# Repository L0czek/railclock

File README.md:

# ESP32 Mainboard (Railclock-derived)

> A general-purpose ESP32-C6 module mainboard originally created for the Railclock project and redesigned as a generic controller and motor-power board.

This PCB exposes 11 GPIOs via JST connectors for sensors and actuators. It can run without an external 5V supply by using an on-board battery charger and a boost converter to create a 12V rail for motors and higher-power peripherals.

## Key Features

- 11 accessible GPIOs on JST connectors (5 ADC-capable ports on the left, 5 digital/drive outputs on the right).
- Left side ports: ADC-capable pins and a selectable 5V supply (powered by on-board 5V regulator/charger when available).
- Right side ports: digitally-driven output stage able to source up to 12V and ~800 mA (per port design limits depend on load and thermal conditions).
- On-board power management:
  - BQ24296M battery charger to accept battery power and produce the 5V line when no external USB is present.
  - PAM2421 boost converter to generate the 12V rail from the battery/5V bus.
- Motor driver: DRV8870 used to drive DC motors from the 12V rail.
- RTC clock MCP7940n with separate battery.

## Hardware Overview

- Connectors:
  - Left JST ports: ADC-capable pins. Expect up to 5V on these when the 5V supply is enabled — do not exceed 5V on ADC inputs.
  - Right JST ports: digital outputs with high-side/outstage to provide up to 12V for actuators.
- Power flow:
  - Primary charge/power management by the BQ24296M allows operation from a Li-ion battery without external 5V.
  - The PAM2421 boost converter takes the available rail and creates the 12V bus used by the outputs and motor driver.
- Motor driver:
  - DRV8870 drives DC motors using the 12V rail; follow the datasheet for current-limiting and heat-sinking requirements.

## Firmware

Firmware for this board is written in Rust and maintained in a separate repository: https://github.com/L0czek/esp32-mainboard

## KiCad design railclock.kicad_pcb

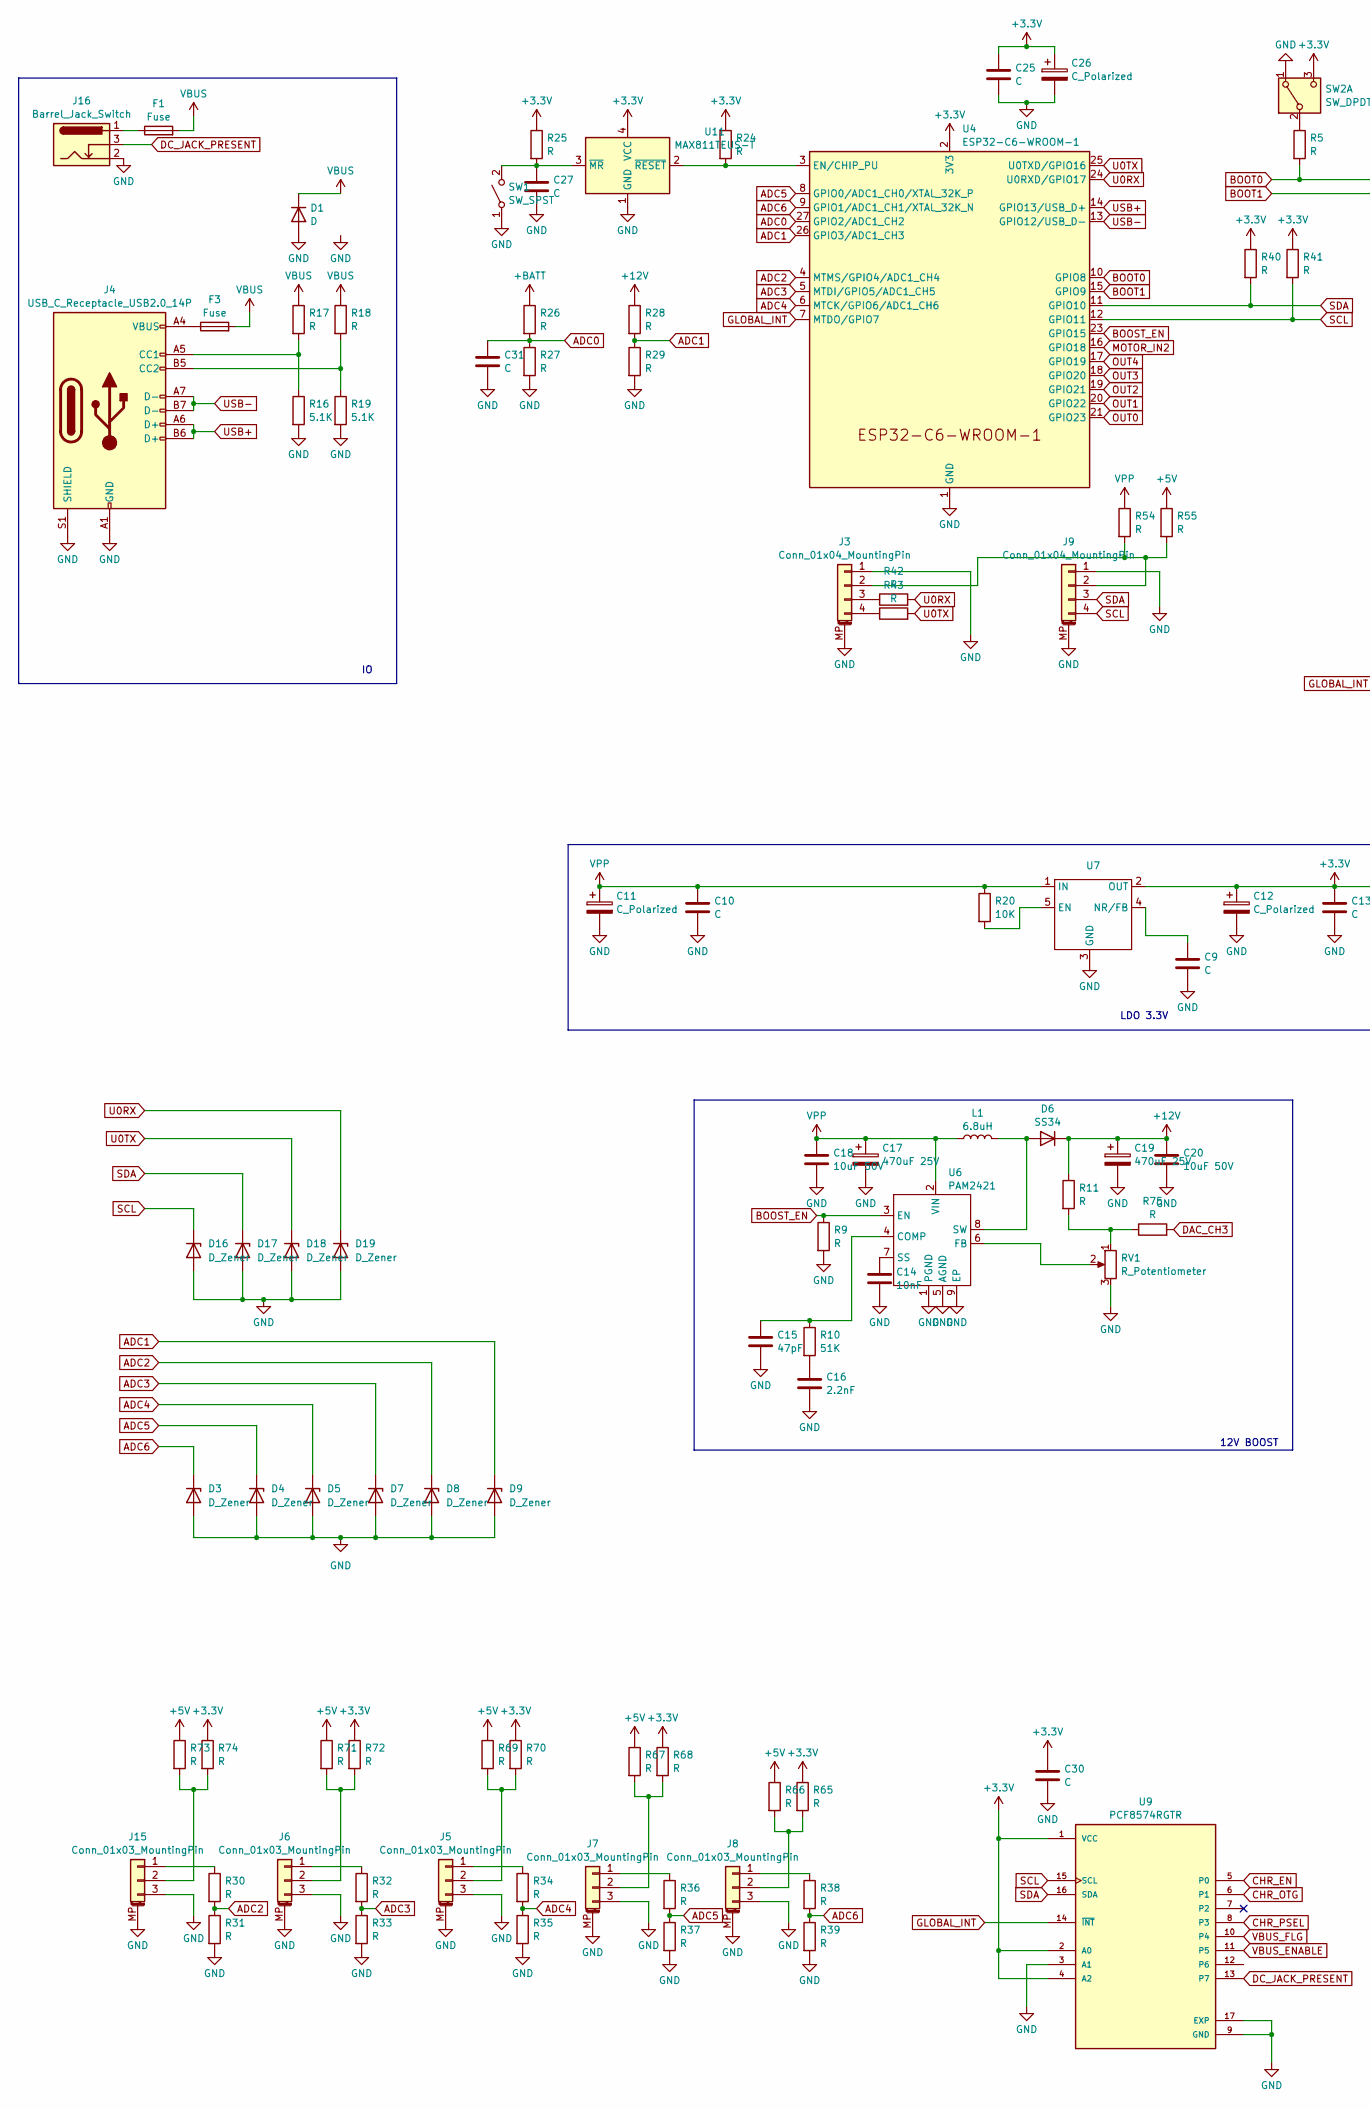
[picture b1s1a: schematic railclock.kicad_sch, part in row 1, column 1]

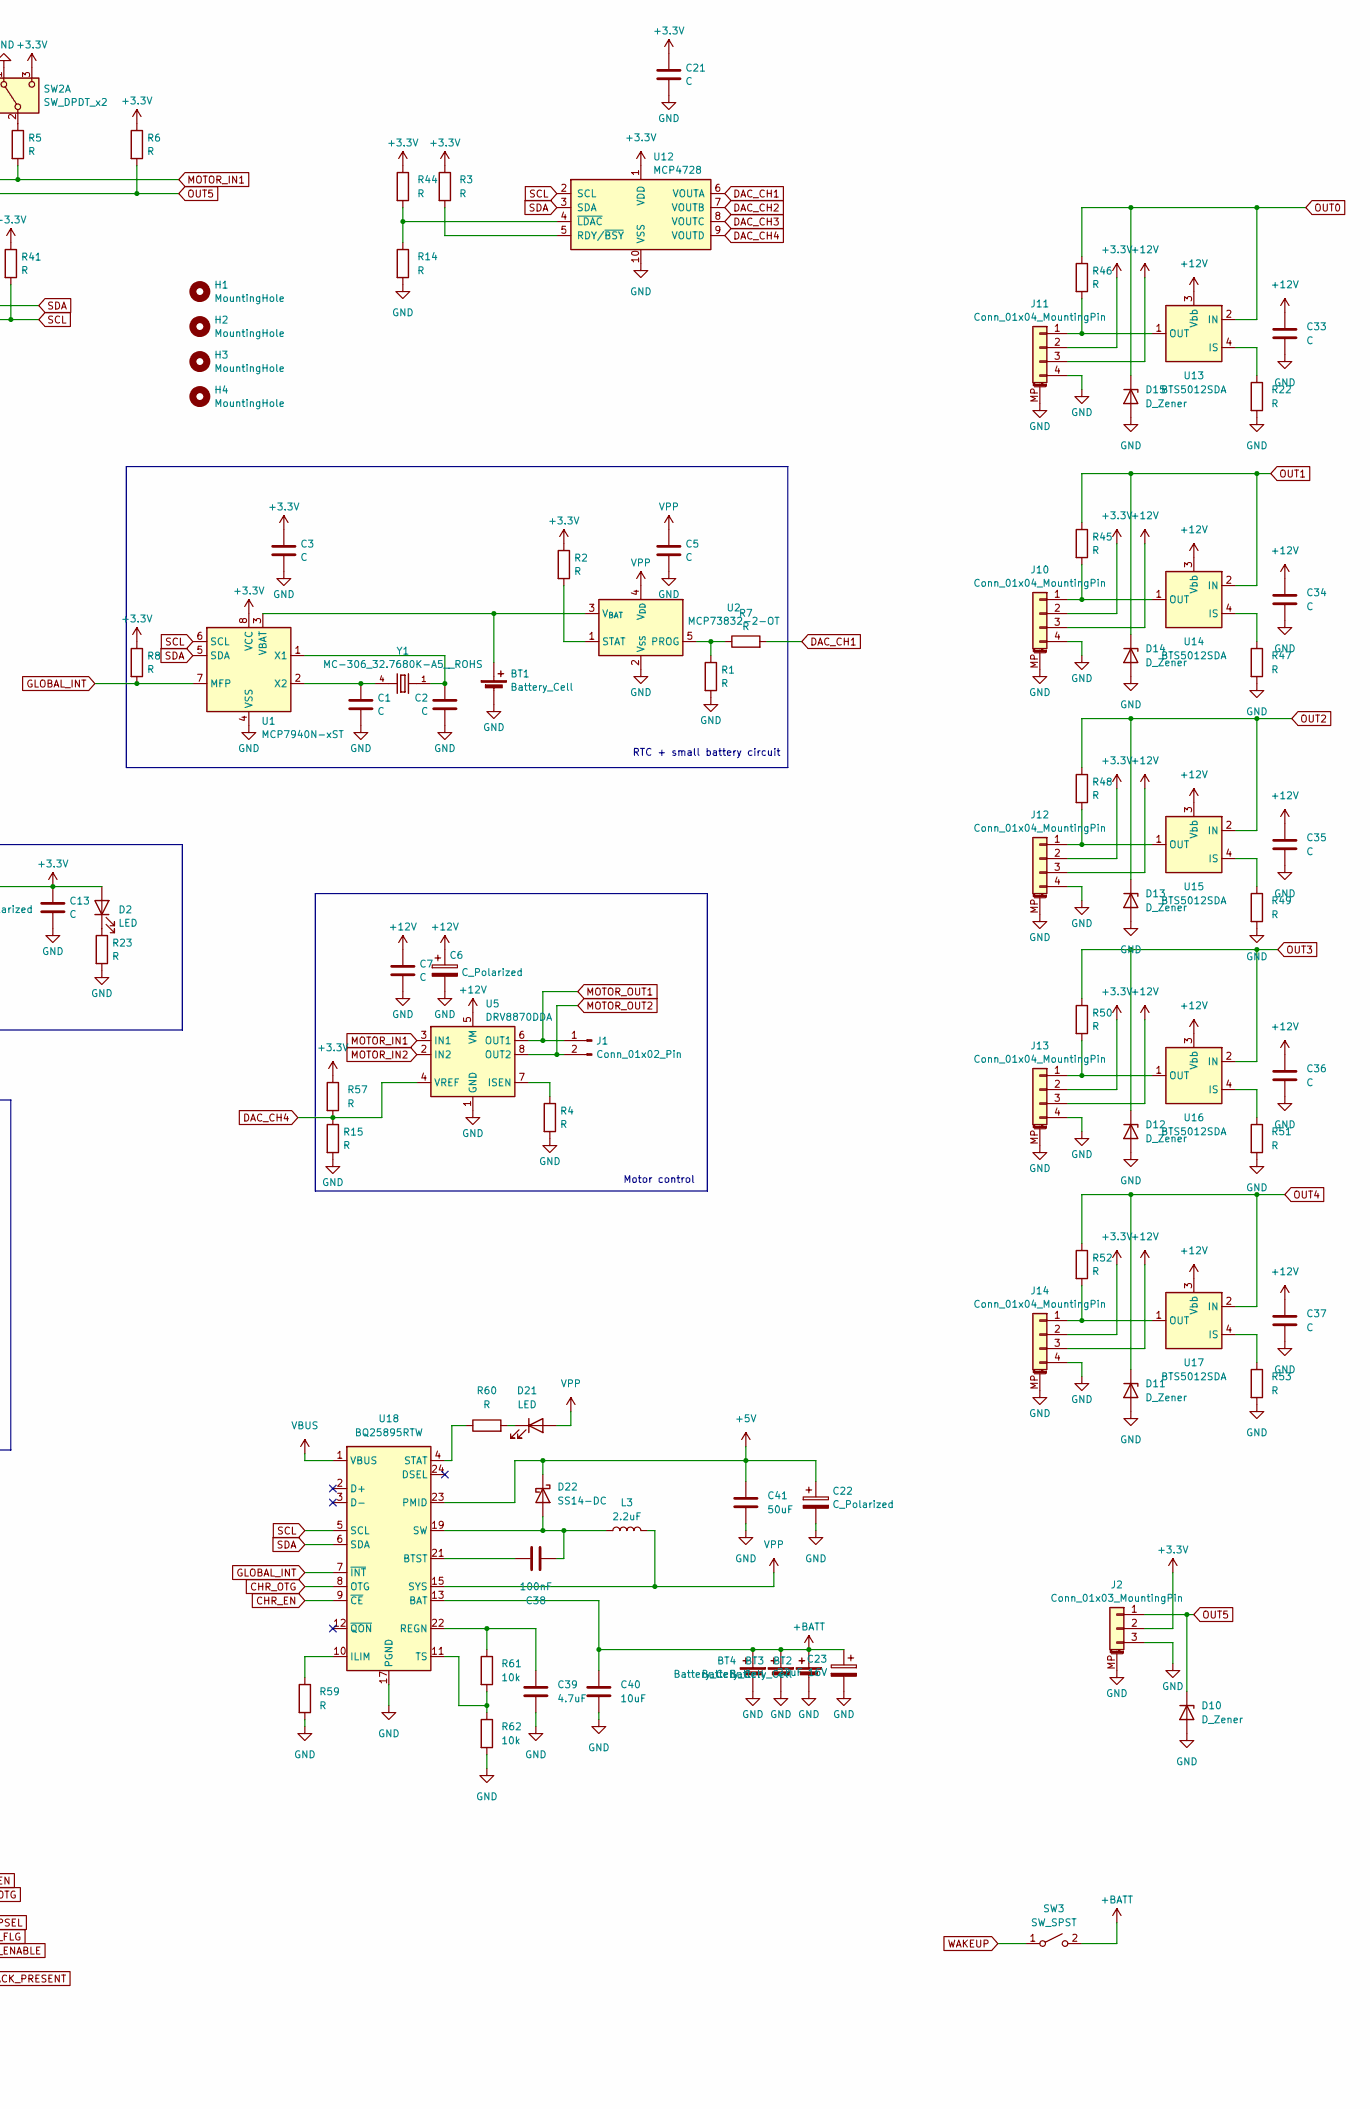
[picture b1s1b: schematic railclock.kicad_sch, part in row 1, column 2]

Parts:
BT1: Battery_Cell; BatteryHolder_Renata_SMTU2032-LF_1x2032
BT2, BT3, BT4: Battery_Cell; BatteryHolder_Keystone_1042_1x18650
C1, C2, C3, C5, C7, C9, C10, C13, C21, C25, C27, C30, C31, C33, C34, C35, C36, C37: C; C_0805_2012Metric
C6, C11, C12, C22: C_Polarized; CP_Elec_8x10
C14: 10nF; C_0805_2012Metric
C15: 47pF; C_0805_2012Metric
C16: 2.2nF; C_0805_2012Metric
C17, C19: 470uF 25V; CP_Elec_8x10
C18, C20: 10uF 50V; C_1210_3225Metric
C23: 22uF 16V; CP_Elec_4x5.3
C26: C_Polarized; CP_EIA-7343-31_Kemet-D
C38: 100nF; C_0805_2012Metric
C39: 4.7uF; C_0805_2012Metric
C40: 10uF; C_0805_2012Metric
C41: 50uF; C_0805_2012Metric
D1: D; D_SMA
D2: LED; LED_1206_3216Metric
D3, D4, D5, D7, D8, D9, D10, D11, D12, D13, D14, D15, D16, D17, D18, D19: D_Zener; D_SOD-323
D6: SS34; D_SMC
D21: LED; LED_0805_2012Metric
D22: SS14-DC; D_SMA
F1, F3: Fuse; Fuse_1206_3216Metric
H1, H2, H3, H4: MountingHole; MountingHole_3.2mm_M3
J1: Conn_01x02_Pin; JST_NV_B02P-NV_1x02_P5.00mm_Vertical
J2, J5, J6, J7, J8, J15: Conn_01x03_MountingPin; JST_PH_S3B-PH-SM4-TB_1x03-1MP_P2.00mm_Horizontal
J3, J9, J10, J11, J12, J13, J14: Conn_01x04_MountingPin; JST_PH_S4B-PH-SM4-TB_1x04-1MP_P2.00mm_Horizontal
J4: USB_C_Receptacle_USB2.0_14P; USB_C_Receptacle_GCT_USB4105-xx-A_16P_TopMnt_Horizontal
J16: Barrel_Jack_Switch; BarrelJack_Horizontal
L1: 6.8uH; L_10.4x10.4_H4.8
L3: 2.2uF; L_Bourns_SRP1038C_10.0x10.0mm
R1, R2, R3, R5, R6, R7, R8, R9, R11, R14, R15, R17, R18, R22, R23, R24, R25, R26, R27, R28, R29, R30, R31, R32, R33, R34, R35, R36, R37, R38, R39, R40, R41, R42, R43, R44, R45, R46, R47, R48, R49, R50, R51, R52, R53, R54, R55, R57, R59, R60, R65, R66, R67, R68, R69, R70, R71, R72, R73, R74, R75: R; R_0805_2012Metric
R4: R; R_2010_5025Metric
R10: 51K; R_0805_2012Metric
R16, R19: 5.1K; R_0805_2012Metric
R20: 10K; R_0805_2012Metric
R61, R62: 10k; R_0805_2012Metric
RV1: R_Potentiometer; Potentiometer_Bourns_3214W_Vertical
SW1: SW_SPST; SW_SPST_B3S-1000
SW2: SW_DPDT_x2; SW_DPDT_CK_JS202011JCQN
SW3: SW_SPST; Panasonic_EVQPUL_EVQPUC
U1: MCP7940N-xST; SOIC-8_3.9x4.9mm_P1.27mm
U2: MCP73832-2-OT; SOT-23-5
U4: ESP32-C6-WROOM-1
U5: DRV8870DDA; Texas_HTSOP-8-1EP_3.9x4.9mm_P1.27mm_EP2.95x4.9mm_Mask2.4x3.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
U6: PAM2421; Diodes_SO-8EP
U7: SOT-223-6
U9: PCF8574RGTR; QFN50P300X300X100-17N; PARTREV J; DigiKey_Part_Number 296-21238-2-ND
U11: MAX811TEUS-T; SOT-143
U12: MCP4728; MSOP-10_3x3mm_P0.5mm
U13, U14, U15, U16, U17: BTS5012SDA; TO-252-4
U18: BQ25895RTW; Texas_RTW_WQFN-24-1EP_4x4mm_P0.5mm_EP2.7x2.7mm_ThermalVias
Y1: MC-306_32.7680K-A5__ROHS; OSCL550P800X320X254-4N

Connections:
+3.3V: C3.1, C12.1, C13.1, C21.1, C25.1, C26.1, C30.1, D2.2 (A), J2.2, J10.2, J11.2, J12.2, J13.2, J14.2, R2.1, R3.1, R6.1, R8.1, R24.1, R25.1, R40.1, R41.1, R44.1, R57.1, R65.1, R68.1, R70.1, R72.1, R74.1, SW2.3 (C), U1.8 (VCC), U4.2 (3V3), U7.2 (OUT), U9.1 (VCC), U9.2 (A0), U9.4 (A2), U11.4 (VCC), U12.1 (VDD)
+5V: C22.1, C41.1, D22.1 (K), R55.1, R66.1, R67.1, R69.1, R71.1, R73.1, U18.23 (PMID)
+12V: C6.1, C7.1, C19.1, C20.1, C33.1, C34.1, C35.1, C36.1, C37.1, D6.1 (K), J10.3, J11.3, J12.3, J13.3, J14.3, R11.1, R28.1, U5.5 (VM), U13.3 (Vbb), U14.3 (Vbb), U15.3 (Vbb), U16.3 (Vbb), U17.3 (Vbb)
+BATT: BT2.1 (+), BT3.1 (+), BT4.1 (+), C23.1, C40.1, R26.1, SW3.2 (B), U18.13 (BAT), U18.14 (BAT)
ADC0: C31.1, R26.2, R27.1, U4.27 (GPIO2/ADC1_CH2)
ADC1: D9.1 (K), R28.2, R29.1, U4.26 (GPIO3/ADC1_CH3)
ADC2: D8.1 (K), R30.2, R31.1, U4.4 (MTMS/GPIO4/ADC1_CH4)
ADC3: D7.1 (K), R32.2, R33.1, U4.5 (MTDI/GPIO5/ADC1_CH5)
ADC4: D5.1 (K), R34.2, R35.1, U4.6 (MTCK/GPIO6/ADC1_CH6)
ADC5: D4.1 (K), R36.2, R37.1, U4.8 (GPIO0/ADC1_CH0/XTAL_32K_P)
ADC6: D3.1 (K), R38.2, R39.1, U4.9 (GPIO1/ADC1_CH1/XTAL_32K_N)
BOOST_EN: R9.1, U4.23 (GPIO15), U6.3 (EN)
BOOT0: R5.2, U4.10 (GPIO8), U5.3 (IN1)
BOOT1: D10.1 (K), J2.1, R6.2, U4.15 (GPIO9)
CHR_EN: U9.5 (P0), U18.9 (~CE)
CHR_OTG: U9.6 (P1), U18.8 (OTG)
CHR_PSEL: U9.8 (P3)
DAC_CH1: R7.2, U12.6 (VOUTA)
DAC_CH2: U12.7 (VOUTB)
DAC_CH3: R75.2, U12.8 (VOUTC)
DAC_CH4: R15.1, R57.2, U5.4 (VREF), U12.9 (VOUTD)
DC_JACK_PRESENT: J16.3, U9.13 (P7)
GLOBAL_INT: R8.2, U1.7 (MFP), U4.7 (MTDO/GPIO7), U9.14 (~INT), U18.7 (~INT)
GND: BT1.2 (-), BT2.2 (-), BT3.2 (-), BT4.2 (-), C1.2, C2.2, C3.2, C5.2, C6.2, C7.2, C9.2, C10.2, C11.2, C12.2, C13.2, C14.2, C15.2, C16.2, C17.2, C18.2, C19.2, C20.2, C21.2, C22.2, C23.2, C25.2, C26.2, C27.2, C30.2, C31.2, C33.2, C34.2, C35.2, C36.2, C37.2, C39.2, C40.2, C41.2, D1.2 (A), D3.2 (A), D4.2 (A), D5.2 (A), D7.2 (A), D8.2 (A), D9.2 (A), D10.2 (A), D11.2 (A), D12.2 (A), D13.2 (A), D14.2 (A), D15.2 (A), D16.2 (A), D17.2 (A), D18.2 (A), D19.2 (A), J2.3, J2.MP (MountPin), J3.1, J3.MP (MountPin), J4.A1 (GND), J4.A12 (GND), J4.B1 (GND), J4.B12 (GND), J4.S1 (SHIELD), J5.3, J5.MP (MountPin), J6.3, J6.MP (MountPin), J7.3, J7.MP (MountPin), J8.3, J8.MP (MountPin), J9.1, J9.MP (MountPin), J10.4, J10.MP (MountPin), J11.4, J11.MP (MountPin), J12.4, J12.MP (MountPin), J13.4, J13.MP (MountPin), J14.4, J14.MP (MountPin), J15.3, J15.MP (MountPin), J16.2, R1.2, R4.2, R9.2, R14.2, R15.2, R16.2, R19.2, R22.2, R23.2, R27.2, R29.2, R31.2, R33.2, R35.2, R37.2, R39.2, R47.2, R49.2, R51.2, R53.2, R59.2, R62.2, RV1.3, SW1.1 (A), SW2.1 (A), U1.4 (VSS), U2.2 (V_{SS}), U4.1 (GND), U4.28 (GND), U4.29 (GND), U5.1 (GND), U5.9 (GND), U6.1 (PGND), U6.5 (AGND), U6.9 (EP), U7.3 (GND), U7.6 (GND), U9.3 (A1), U9.9 (GND), U9.17 (EXP), U11.1 (GND), U12.10 (VSS), U18.17 (PGND), U18.18 (PGND), U18.25 (PGND)
MOTOR_IN2: U4.16 (GPIO18), U5.2 (IN2)
MOTOR_OUT1: J1.1, U5.6 (OUT1)
MOTOR_OUT2: J1.2, U5.8 (OUT2)
unnamed: BT1.1 (+), U1.3 (VBAT), U2.3 (V_{BAT})
unnamed: C16.1, R10.2
unnamed: D2.1 (K), R23.1
unnamed: D6.2 (A), L1.2, U6.8 (SW)
unnamed: D21.1 (K), R60.2
unnamed: C38.1, D22.2 (A), L3.1, U18.19 (SW), U18.20 (SW)
unnamed: F1.1, J16.1
unnamed: F3.1, J4.A4 (VBUS), J4.A9 (VBUS), J4.B4 (VBUS), J4.B9 (VBUS)
unnamed: J3.2, J9.2, R54.2, R55.2
unnamed: J3.3, R42.1
unnamed: J3.4, R43.1
unnamed: J4.A5 (CC1), R16.1, R17.2
unnamed: J4.B5 (CC2), R18.2, R19.1
unnamed: J5.1, R34.1
unnamed: J5.2, R69.2, R70.2
unnamed: J6.1, R32.1
unnamed: J6.2, R71.2, R72.2
unnamed: J7.1, R36.1
unnamed: J7.2, R67.2, R68.2
unnamed: J8.1, R38.1
unnamed: J8.2, R65.2, R66.2
unnamed: J10.1, R45.2, U14.1 (OUT), U14.5 (OUT)
unnamed: J11.1, R46.2, U13.1 (OUT), U13.5 (OUT)
unnamed: J12.1, R48.2, U15.1 (OUT), U15.5 (OUT)
unnamed: J13.1, R50.2, U16.1 (OUT), U16.5 (OUT)
unnamed: J14.1, R52.2, U17.1 (OUT), U17.5 (OUT)
unnamed: J15.1, R30.1
unnamed: J15.2, R73.2, R74.2
unnamed: R11.2, R75.1, RV1.1
unnamed: C27.1, R25.2, SW1.2 (B), U11.3 (~MR)
unnamed: R5.1, SW2.2 (B)
unnamed: C2.1, U1.1 (X1), Y1.1
unnamed: C1.1, U1.2 (X2), Y1.4
unnamed: R1.1, R7.1, U2.5 (PROG)
unnamed: R2.2, U2.1 (STAT)
unnamed: R4.1, U5.7 (ISEN)
unnamed: C15.1, R10.1, U6.4 (COMP)
unnamed: RV1.2, U6.6 (FB)
unnamed: C14.1, U6.7 (SS)
unnamed: R20.2, U7.5 (EN)
unnamed: C9.1, U7.4 (NR/FB)
unnamed: R24.2, U4.3 (EN/CHIP_PU), U11.2 (~RESET)
unnamed: R3.2, U12.5 (RDY/~BSY)
unnamed: R14.1, R44.2, U12.4 (~LDAC)
unnamed: R22.1, U13.4 (IS)
unnamed: R47.1, U14.4 (IS)
unnamed: R49.1, U15.4 (IS)
unnamed: R51.1, U16.4 (IS)
unnamed: R53.1, U17.4 (IS)
unnamed: C38.2, U18.21 (BTST)
unnamed: R59.1, U18.10 (ILIM)
unnamed: C39.1, R61.1, U18.22 (REGN)
unnamed: R60.1, U18.4 (STAT)
unnamed: R61.2, R62.1, U18.11 (TS)
OUT0: D15.1 (K), R46.1, U4.21 (GPIO23), U13.2 (IN)
OUT1: D14.1 (K), R45.1, U4.20 (GPIO22), U14.2 (IN)
OUT2: D13.1 (K), R48.1, U4.19 (GPIO21), U15.2 (IN)
OUT3: D12.1 (K), R50.1, U4.18 (GPIO20), U16.2 (IN)
OUT4: D11.1 (K), R52.1, U4.17 (GPIO19), U17.2 (IN)
SCL: D16.1 (K), J9.4, R41.2, U1.6 (SCL), U4.12 (GPIO11), U9.15 (SCL), U12.2 (SCL), U18.5 (SCL)
SDA: D17.1 (K), J9.3, R40.2, U1.5 (SDA), U4.11 (GPIO10), U9.16 (SDA), U12.3 (SDA), U18.6 (SDA)
U0RX: D19.1 (K), R42.2, U4.24 (U0RXD/GPIO17)
U0TX: D18.1 (K), R43.2, U4.25 (U0TXD/GPIO16)
USB+: J4.A6 (D+), J4.B6 (D+), U4.14 (GPIO13/USB_D+)
USB-: J4.A7 (D-), J4.B7 (D-), U4.13 (GPIO12/USB_D-)
VBUS: D1.1 (K), F1.2, F3.2, R17.1, R18.1, U18.1 (VBUS)
VBUS_ENABLE: U9.11 (P5)
VBUS_FLG: U9.10 (P4)
VPP: C5.1, C10.1, C11.1, C17.1, C18.1, D21.2 (A), L1.1, L3.2, R20.1, R54.1, U2.4 (V_{DD}), U6.2 (VIN), U7.1 (IN), U18.15 (SYS), U18.16 (SYS)
WAKEUP: SW3.1 (A)

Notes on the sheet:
Motor control
12V BOOST
LDO 3.3V
RTC + small battery circuit

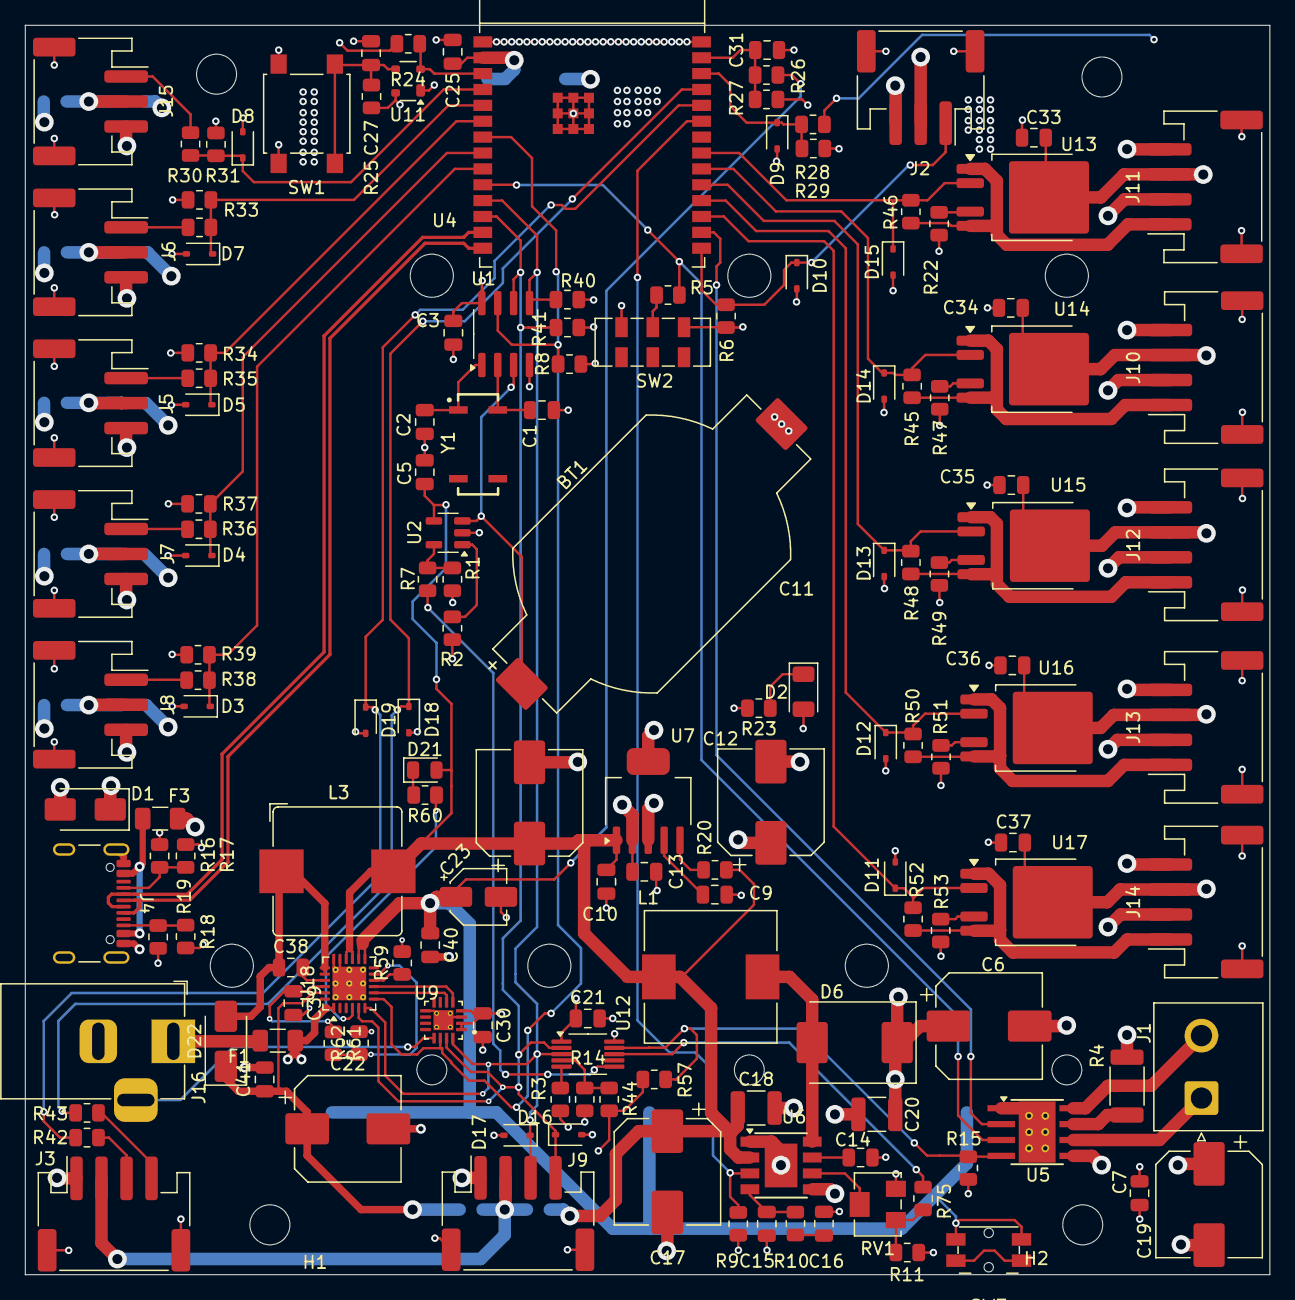
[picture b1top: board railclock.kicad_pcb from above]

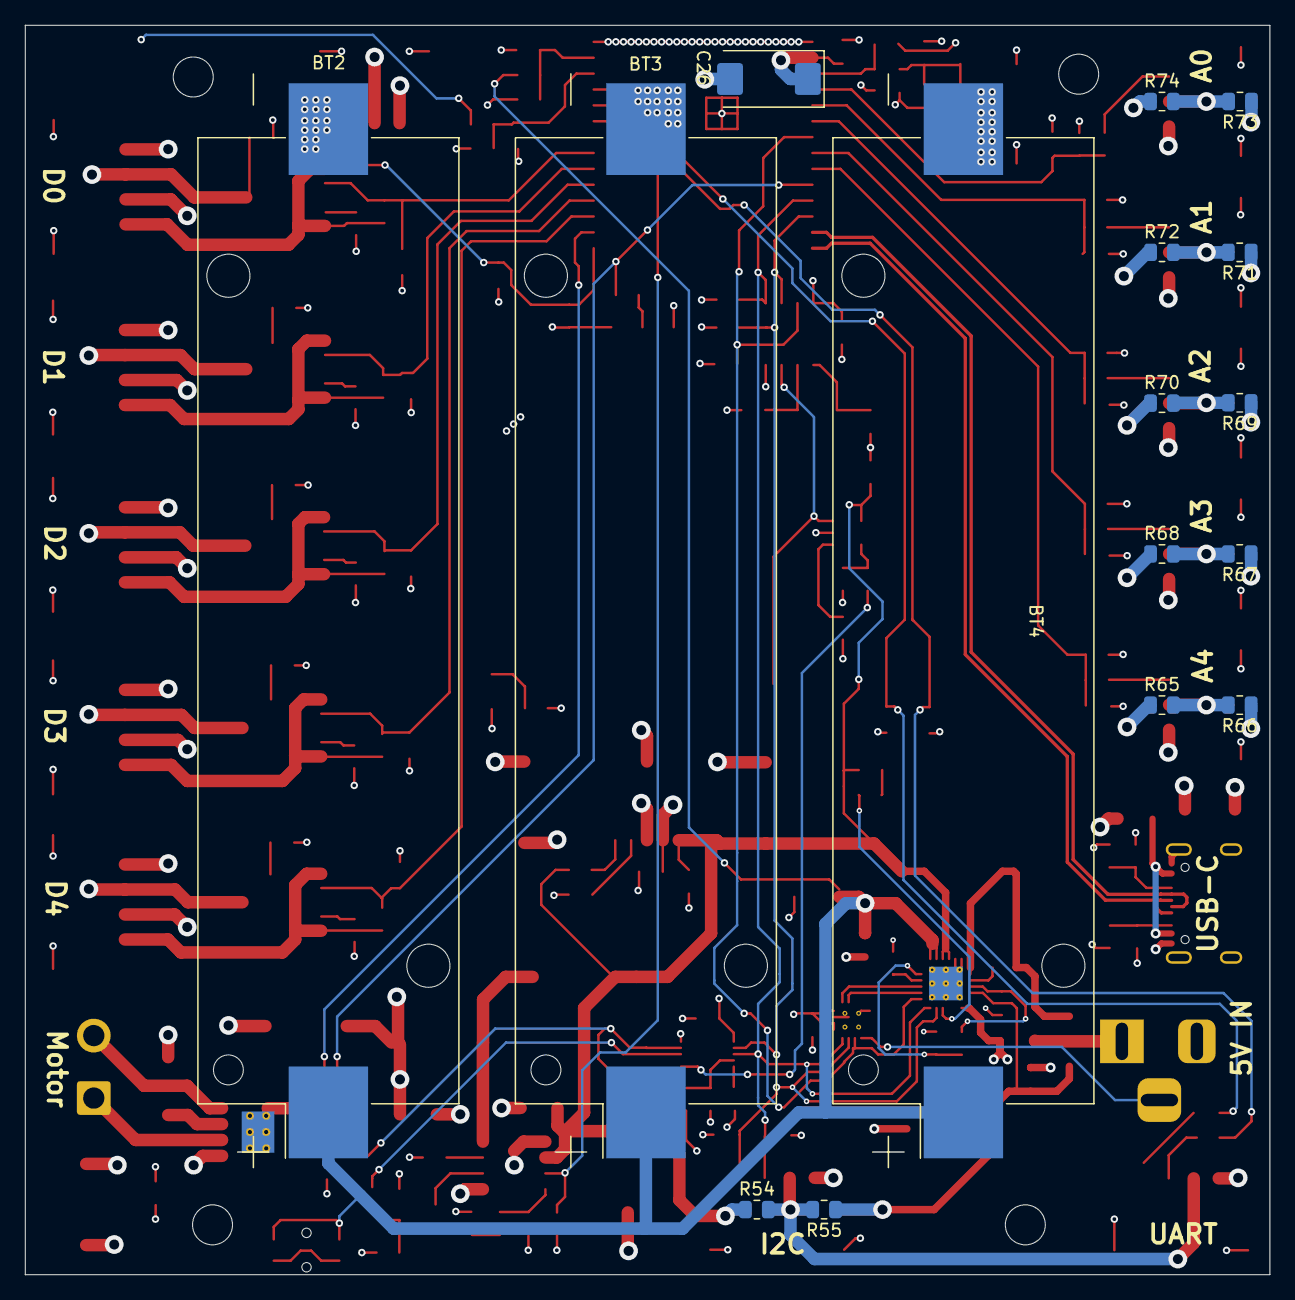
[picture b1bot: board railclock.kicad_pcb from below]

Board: 4 copper layers, 99.6 x 99.9 mm, 172 parts (16 on the bottom side), 92 nets.

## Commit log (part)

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2025-06-27 Add railclock pcb
2025-06-29 Fix issues with first version
2025-07-01 Add option to choose which volatage is avaialble on the I2C connector
2025-09-08 Update board, rewire digital connections
2025-09-09 Add transils to A-D pins, fix vbus detection
2025-09-10 Add transils fix vbus detection
2025-09-13 Replace UART connector
2025-10-07 Fix foorptints references
2025-10-09 Add element values and some fixes
2025-10-10 Reroute to 4 layer pcb
2025-10-16 Rework to new kanapka
2025-11-11 Schematic marking updates
2025-11-12 more values
2025-11-30 Add R21 value
2026-01-13 Add README
2026-04-19 Fix VBUS detection and add wakeup button
